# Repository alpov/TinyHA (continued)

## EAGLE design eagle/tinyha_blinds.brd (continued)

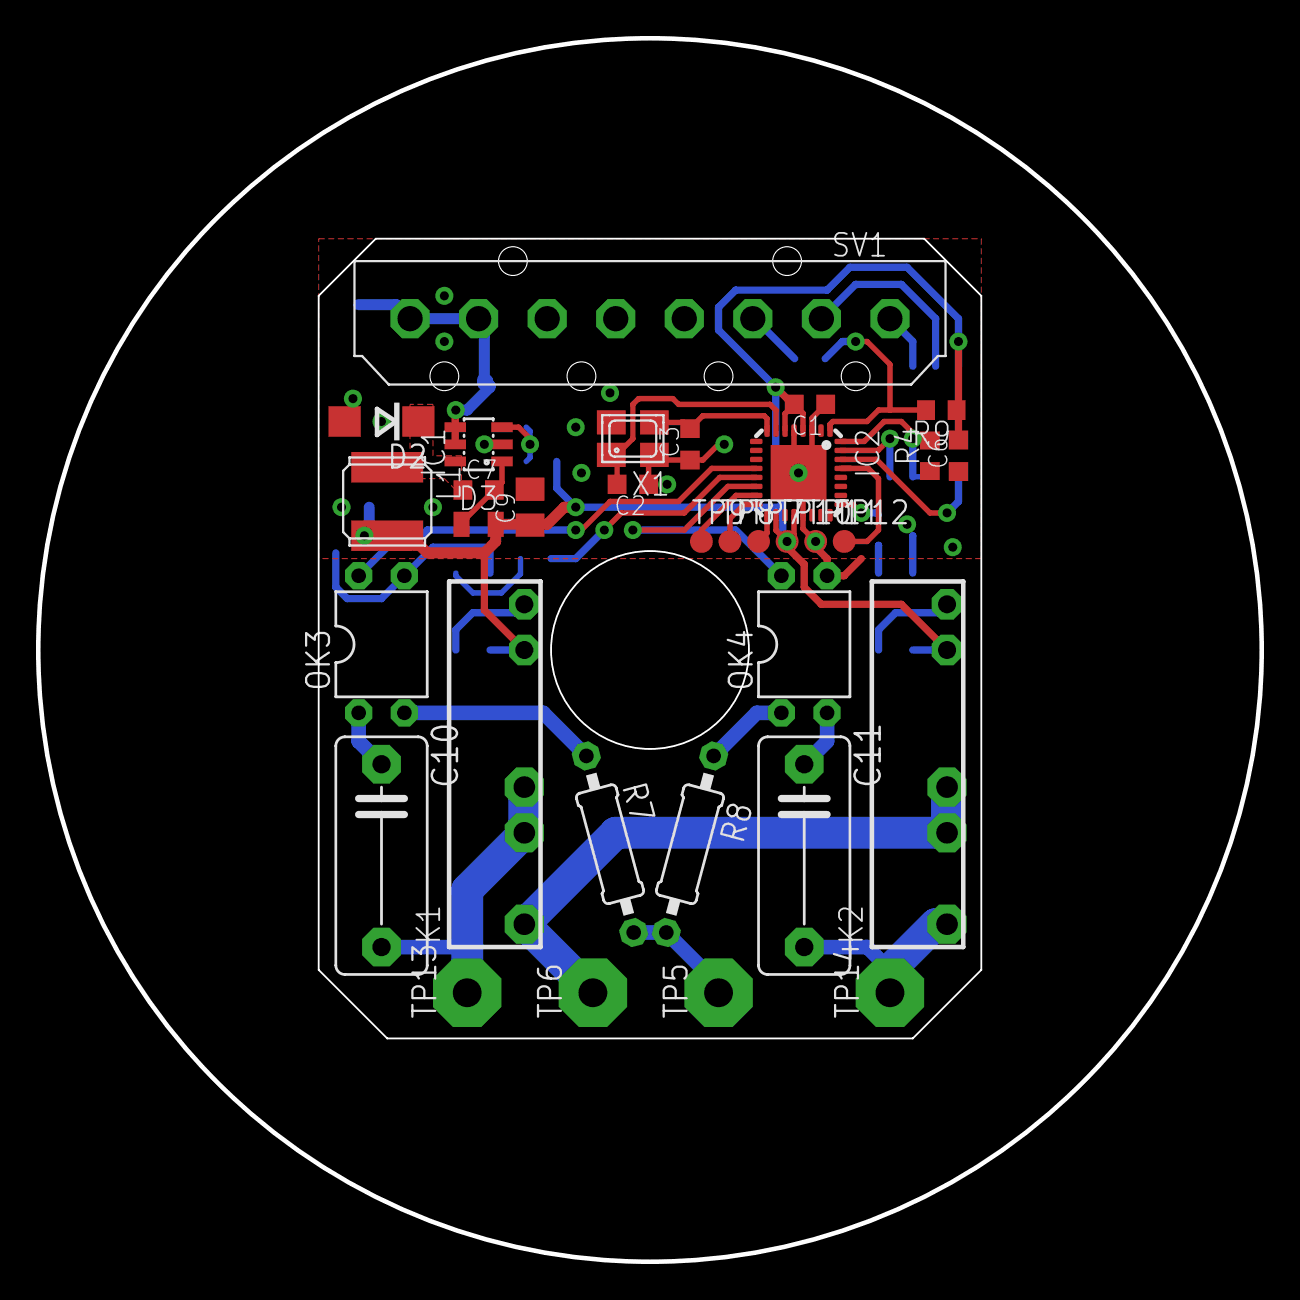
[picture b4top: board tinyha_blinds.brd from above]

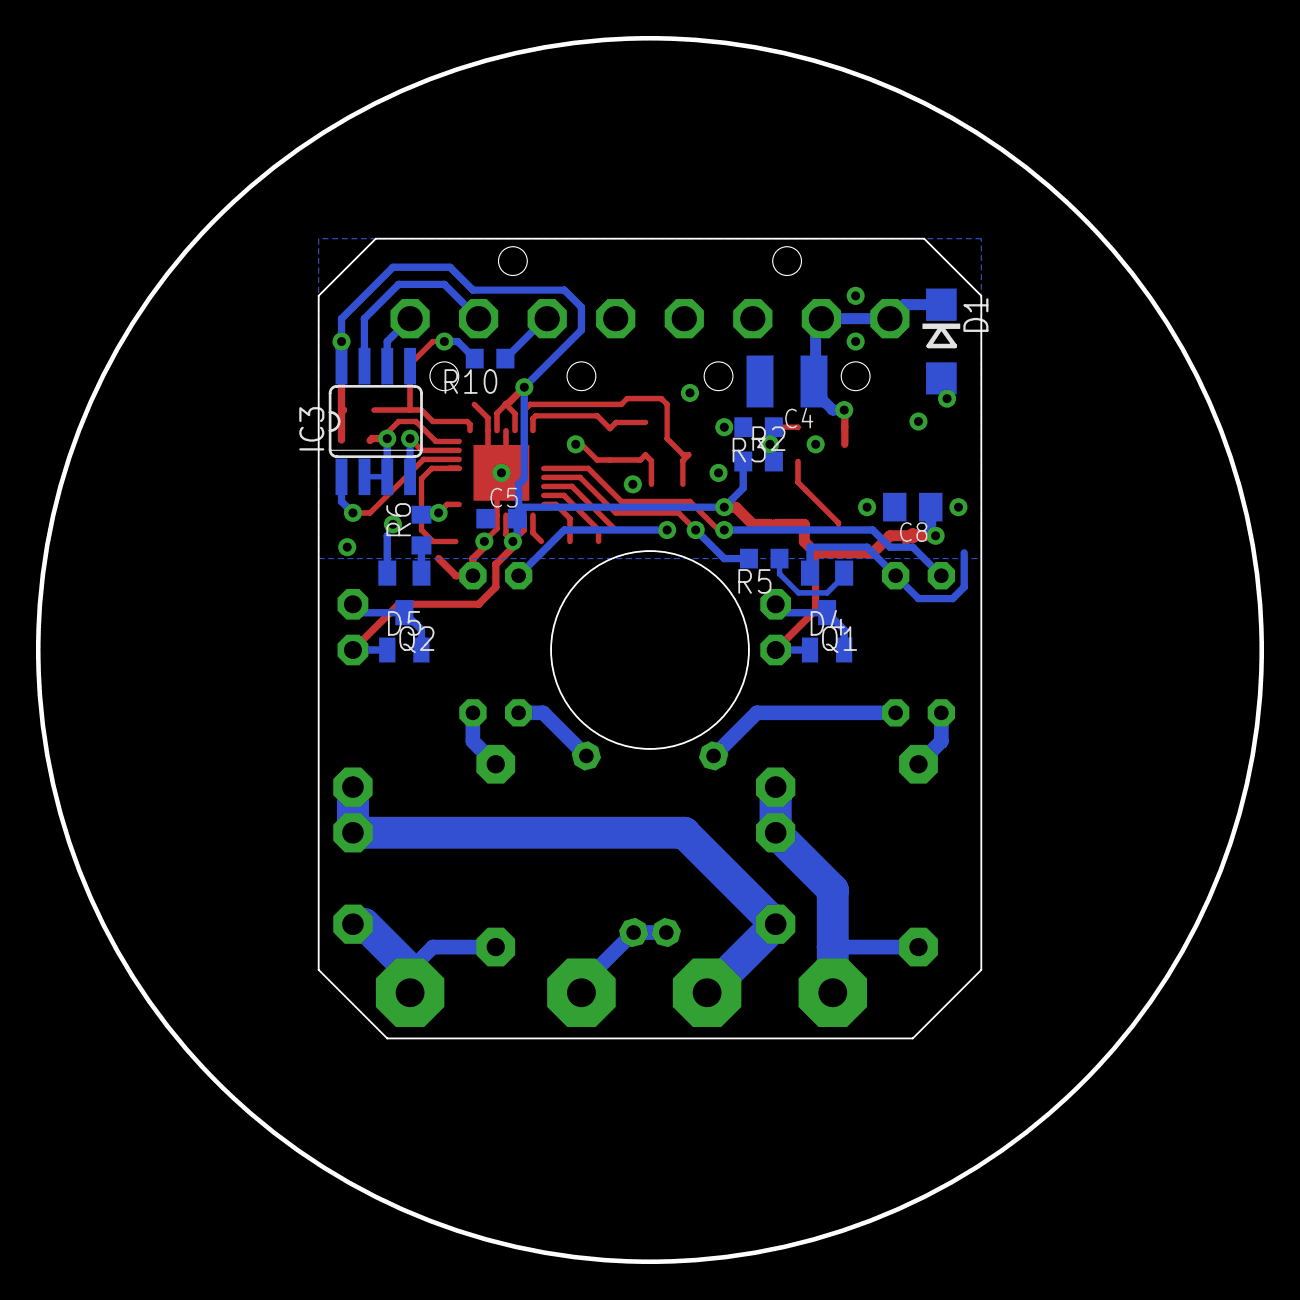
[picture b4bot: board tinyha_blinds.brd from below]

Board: 2 copper layers, 68.0 x 68.0 mm, 47 parts (14 on the bottom side), 35 nets.

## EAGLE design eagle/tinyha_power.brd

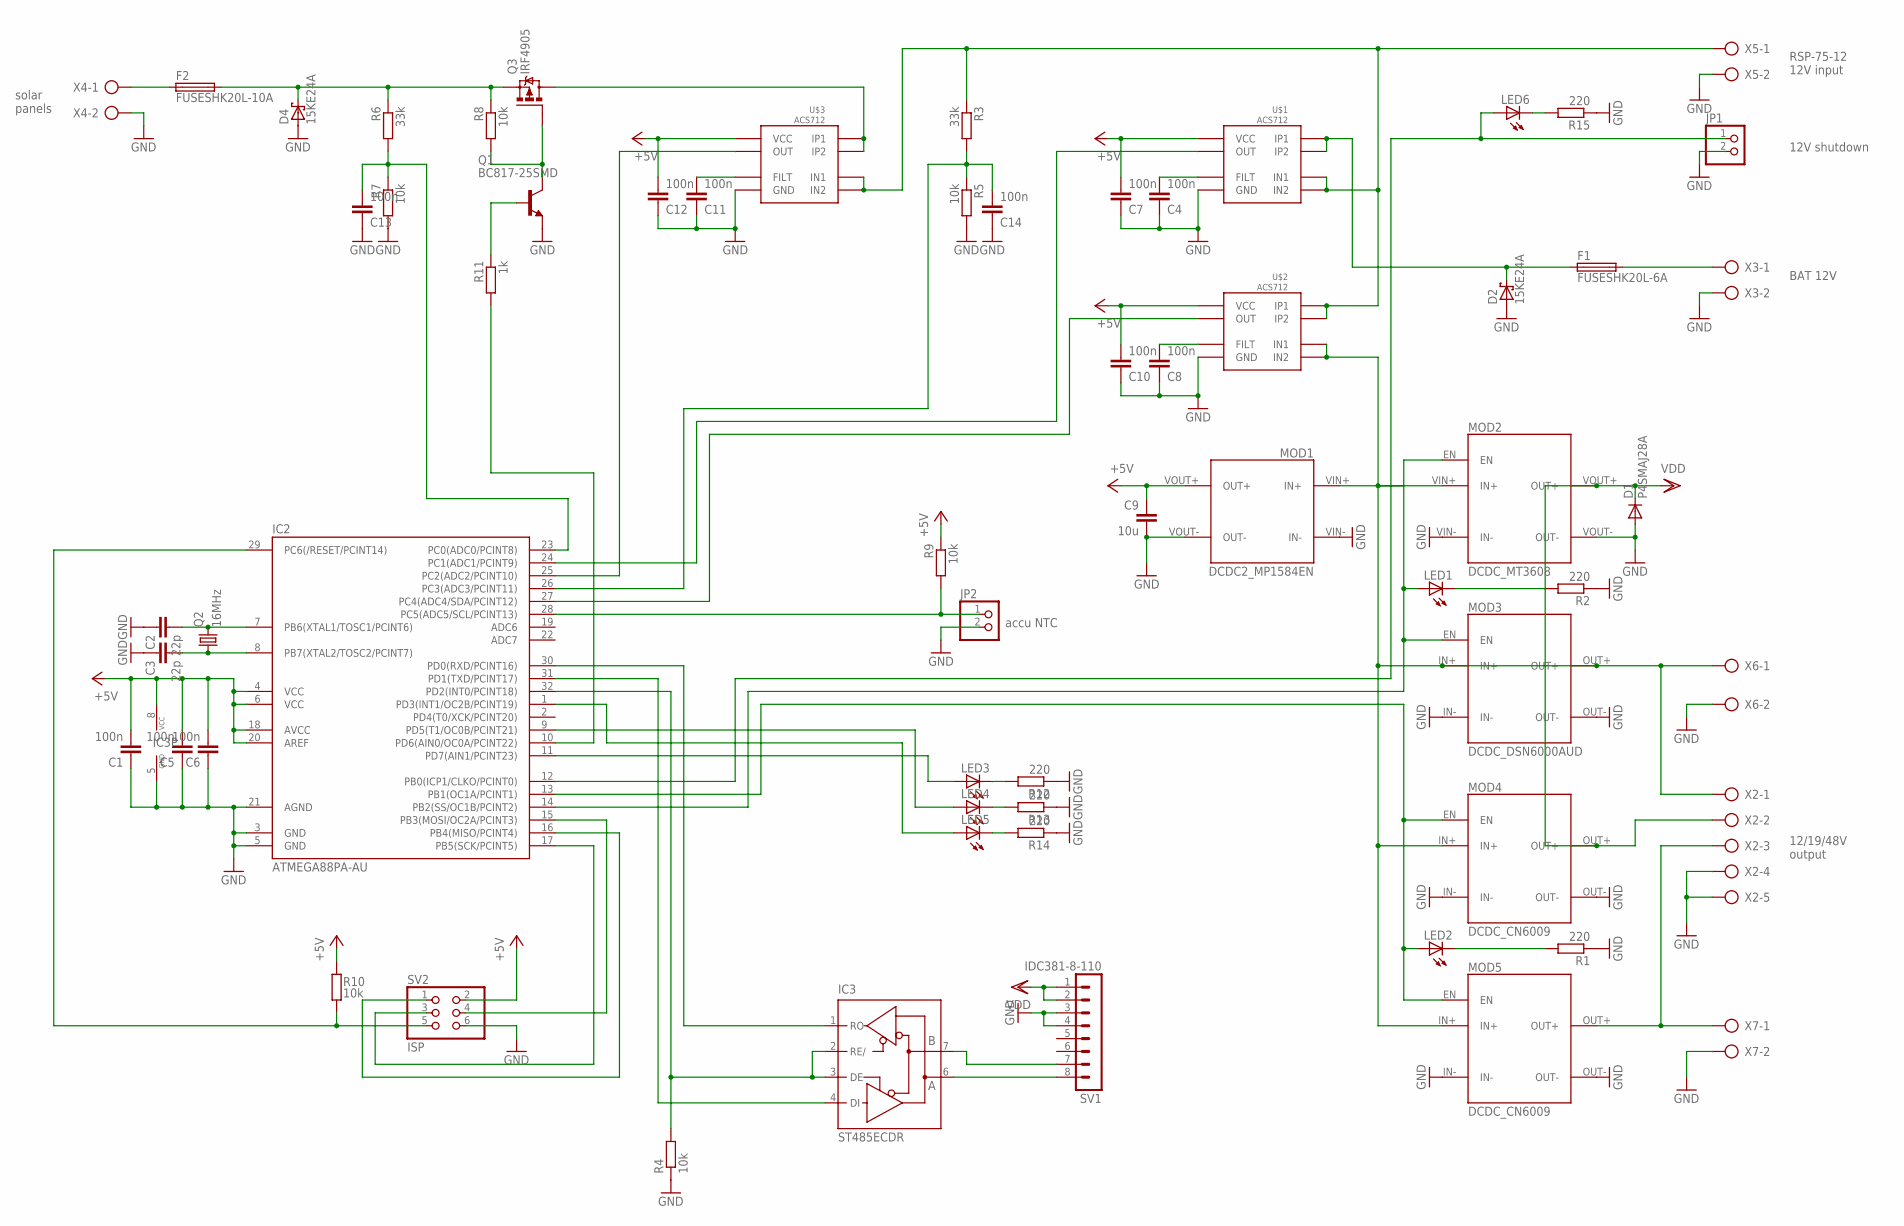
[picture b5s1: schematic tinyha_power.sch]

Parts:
C1, C5, C6: 100n; C0805K
C2, C3: 22p; C0805K
C4, C7, C8, C10, C11, C12, C13, C14: 100n; C0805
C9: 10u; C0805K
D1: P4SMAJ28A; DO214AC
D2, D4: 15KE24A; CB429-17
F1: FUSESHK20L-6A; SHK20L
F2: FUSESHK20L-10A; SHK20L
IC2: ATMEGA88PA-AU; TQFP32-08
IC3: ST485ECDR; SO08
JP1, JP2: PINHD-1X2; 1X02
LED1, LED2, LED3, LED4, LED5, LED6: LED3MM
MOD1: DCDC2_MP1584EN; DCDC_MP1584EN
MOD2: DCDC_MT3608
MOD3: DCDC_DSN6000AUD
MOD4, MOD5: DCDC_CN6009
Q1: BC817-25SMD; SOT23-BEC
Q2: 16MHz; HC49/S
Q3: IRF4905; TO220BH
R1, R2, R12, R13, R14, R15: 220; R0805
R3, R6: 33k; R0805
R4, R5, R7, R8, R9, R10: 10k; R0805
R11: 1k; R0805
SV1: IDC381-8-110; IDC381-8
SV2: ISP; 2X03/H
U$1, U$2, U$3: ACS712; SO8
X2: AK500/5
X3, X4, X5, X6, X7: AK500/2

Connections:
+5V: C1.2, C5.2, C6.2, C7.2, C9.1, C10.2, C12.2, IC2.4 (VCC), IC2.6 (VCC), IC2.18 (AVCC), IC2.20 (AREF), IC3.8 (VCC), MOD1.VOUT+ (OUT+), R9.1, R10.1, SV2.2, U$1.8 (VCC), U$2.8 (VCC), U$3.8 (VCC)
DIR: IC2.32 (PD2(INT0/PCINT18)), IC3.2 (RE/), IC3.3 (DE), R4.2
GND: C1.1, C2.1, C3.1, C4.1, C5.1, C6.1, C7.1, C8.1, C9.2, C10.1, C11.1, C12.1, C13.1, C14.1, D1.A, D2.A, D4.A, IC2.3 (GND), IC2.5 (GND), IC2.21 (AGND), IC3.5 (GND), JP1.2, JP2.2, MOD1.VIN- (IN-), MOD1.VOUT- (OUT-), MOD2.VIN- (IN-), MOD2.VOUT- (OUT-), MOD3.IN-, MOD3.OUT-, MOD4.IN-, MOD4.OUT-, MOD5.IN-, MOD5.OUT-, Q1.E, R1.1, R2.1, R4.1, R5.2, R7.2, R12.1, R13.1, R14.1, R15.1, SV1.3, SV1.4, SV2.6, U$1.5 (GND), U$2.5 (GND), U$3.5 (GND), X2.4, X2.5, X3.2, X4.2, X5.2, X6.2, X7.2
MOSI: IC2.15 (PB3(MOSI/OC2A/PCINT3)), SV2.4
unnamed: D4.C, F2.2A (2), Q3.S, R6.1, R8.1
unnamed: IC2.13 (PB1(OC1A/PCINT1)), LED2.A, MOD4.EN, MOD5.EN
unnamed: IC2.14 (PB2(SS/OC1B/PCINT2)), LED1.A, MOD2.EN, MOD3.EN
unnamed: LED2.K (C), R1.2
unnamed: LED1.K (C), R2.2
unnamed: IC2.11 (PD7(AIN1/PCINT23)), LED3.A
unnamed: C4.2, U$1.6 (FILT)
unnamed: D2.C, F1.1A (1), U$1.1 (IP1), U$1.2 (IP2)
unnamed: IC2.9 (PD5(T1/OC0B/PCINT21)), LED4.A
unnamed: IC3.7 (B), SV1.7
unnamed: LED6.K (C), R15.2
unnamed: C8.2, U$2.6 (FILT)
unnamed: IC3.6 (A), SV1.8
unnamed: MOD5.OUT+, X2.3, X7.1
unnamed: F1.2A (2), X3.1
unnamed: IC2.1 (PD3(INT1/OC2B/PCINT19)), LED5.A
unnamed: IC2.28 (PC5(ADC5/SCL/PCINT13)), JP2.1, R9.2
unnamed: MOD1.VIN+ (IN+), MOD2.VIN+ (IN+), MOD3.IN+, MOD3.OUT+, MOD4.IN+, MOD5.IN+, U$2.3 (IN1), U$2.4 (IN2), X2.1, X6.1
unnamed: C11.2, U$3.6 (FILT)
unnamed: C3.2, IC2.8 (PB7(XTAL2/TOSC2/PCINT7)), Q2.1
unnamed: Q1.C, Q3.G, R8.2
unnamed: C14.2, IC2.26 (PC3(ADC3/PCINT11)), R3.2, R5.1
unnamed: IC2.24 (PC1(ADC1/PCINT9)), U$1.7 (OUT)
unnamed: IC2.27 (PC4(ADC4/SDA/PCINT12)), U$2.7 (OUT)
unnamed: F2.1A (1), X4.1
unnamed: R3.1, U$1.3 (IN1), U$1.4 (IN2), U$2.1 (IP1), U$2.2 (IP2), U$3.3 (IN1), U$3.4 (IN2), X5.1
unnamed: C2.2, IC2.7 (PB6(XTAL1/TOSC1/PCINT6)), Q2.2
unnamed: Q3.D, U$3.1 (IP1), U$3.2 (IP2)
unnamed: IC2.25 (PC2(ADC2/PCINT10)), U$3.7 (OUT)
unnamed: C13.2, IC2.23 (PC0(ADC0/PCINT8)), R6.2, R7.1
unnamed: Q1.B, R11.1
unnamed: IC2.10 (PD6(AIN0/OC0A/PCINT22)), R11.2
unnamed: LED3.K (C), R12.2
unnamed: LED4.K (C), R13.2
unnamed: LED5.K (C), R14.2
unnamed: IC2.12 (PB0(ICP1/CLKO/PCINT0)), JP1.1, LED6.A
RESET: IC2.29 (PC6(/RESET/PCINT14)), R10.2, SV2.5
RXD: IC2.30 (PD0(RXD/PCINT16)), IC3.1 (RO)
SCK: IC2.17 (PB5(SCK/PCINT5)), SV2.3
TXD: IC2.31 (PD1(TXD/PCINT17)), IC3.4 (DI)
UH: IC2.16 (PB4(MISO/PCINT4)), SV2.1
VDD: D1.C, MOD2.VOUT+ (OUT+), MOD4.OUT+, SV1.1, SV1.2, X2.2

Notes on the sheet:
RSP-75-12 12V input
12/19/48V output
BAT 12V
solar panels
12V shutdown
accu NTC

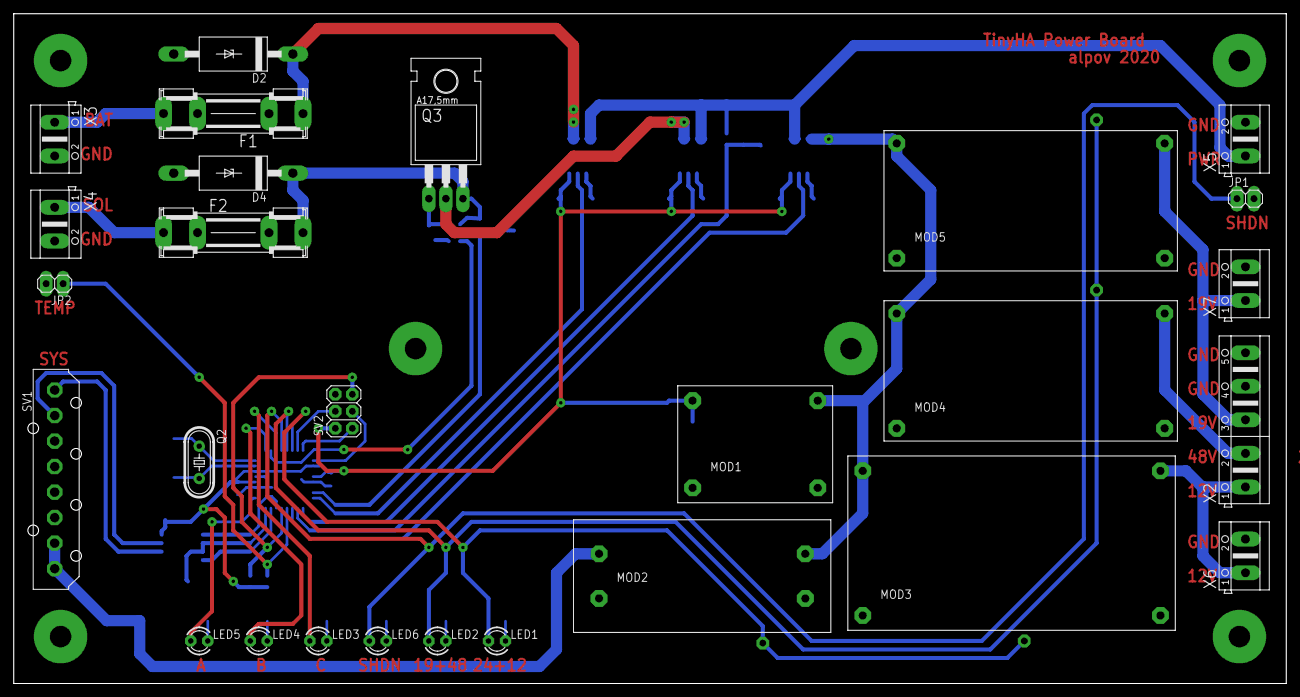
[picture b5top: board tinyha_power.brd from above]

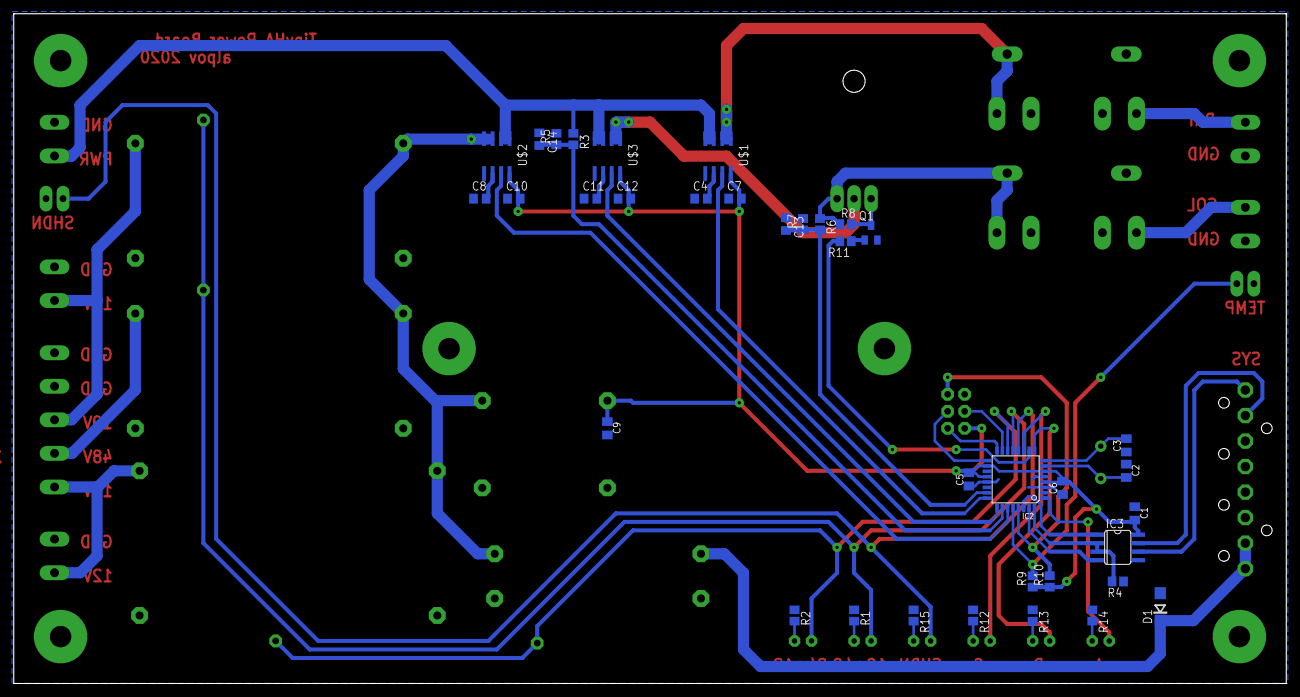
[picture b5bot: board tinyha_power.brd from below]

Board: 3 copper layers, 190.0 x 100.0 mm, 63 parts (36 on the bottom side), 46 nets.

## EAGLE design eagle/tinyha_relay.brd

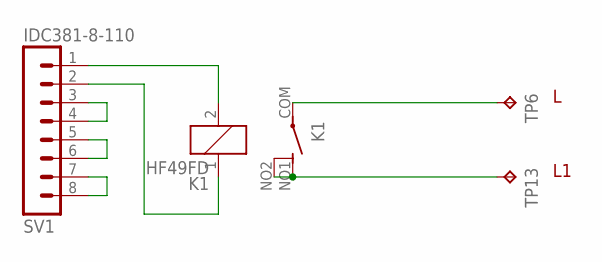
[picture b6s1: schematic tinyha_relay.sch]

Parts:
K1: HF49FD; HF49D
SV1: IDC381-8-110; IDC381-8
TP6, TP13: TP230; P1-20

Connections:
unnamed: SV1.5, SV1.6
unnamed: K1.NO1 (S1), K1.NO2 (S2), TP13.TP
unnamed: SV1.3, SV1.4
unnamed: K1.2, SV1.1
unnamed: K1.1, SV1.2
unnamed: SV1.7, SV1.8
unnamed: K1.COM, TP6.TP

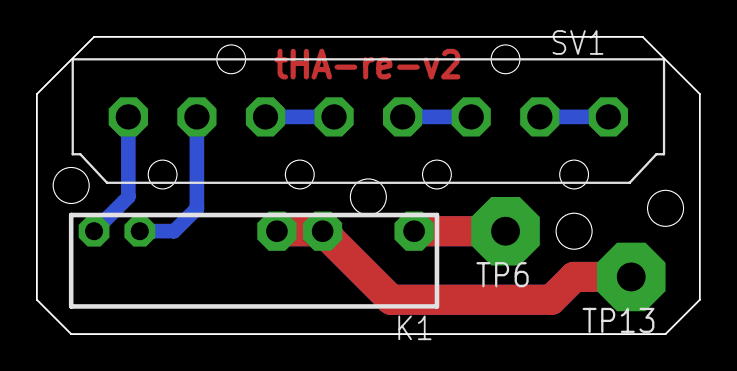
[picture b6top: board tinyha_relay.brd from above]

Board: 2 copper layers, 36.8 x 16.5 mm, 4 parts (0 on the bottom side), 7 nets.

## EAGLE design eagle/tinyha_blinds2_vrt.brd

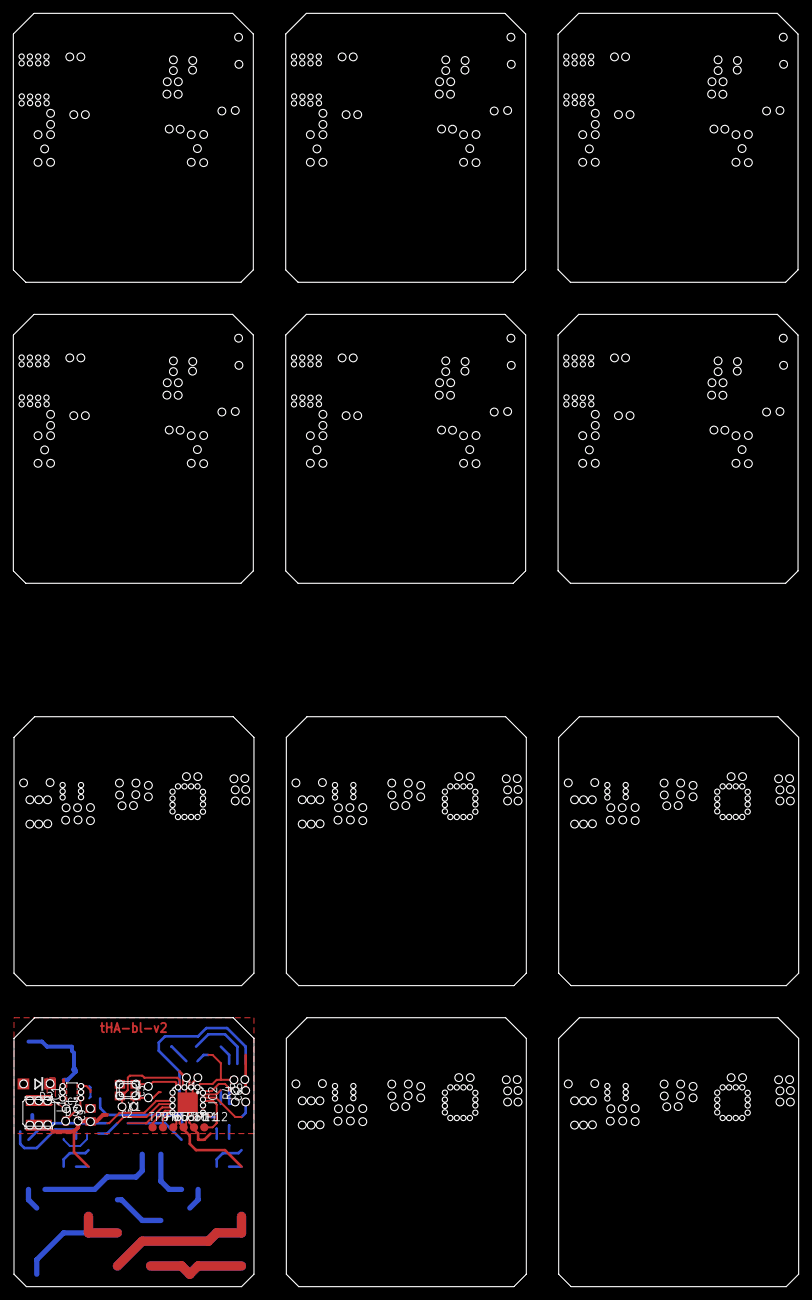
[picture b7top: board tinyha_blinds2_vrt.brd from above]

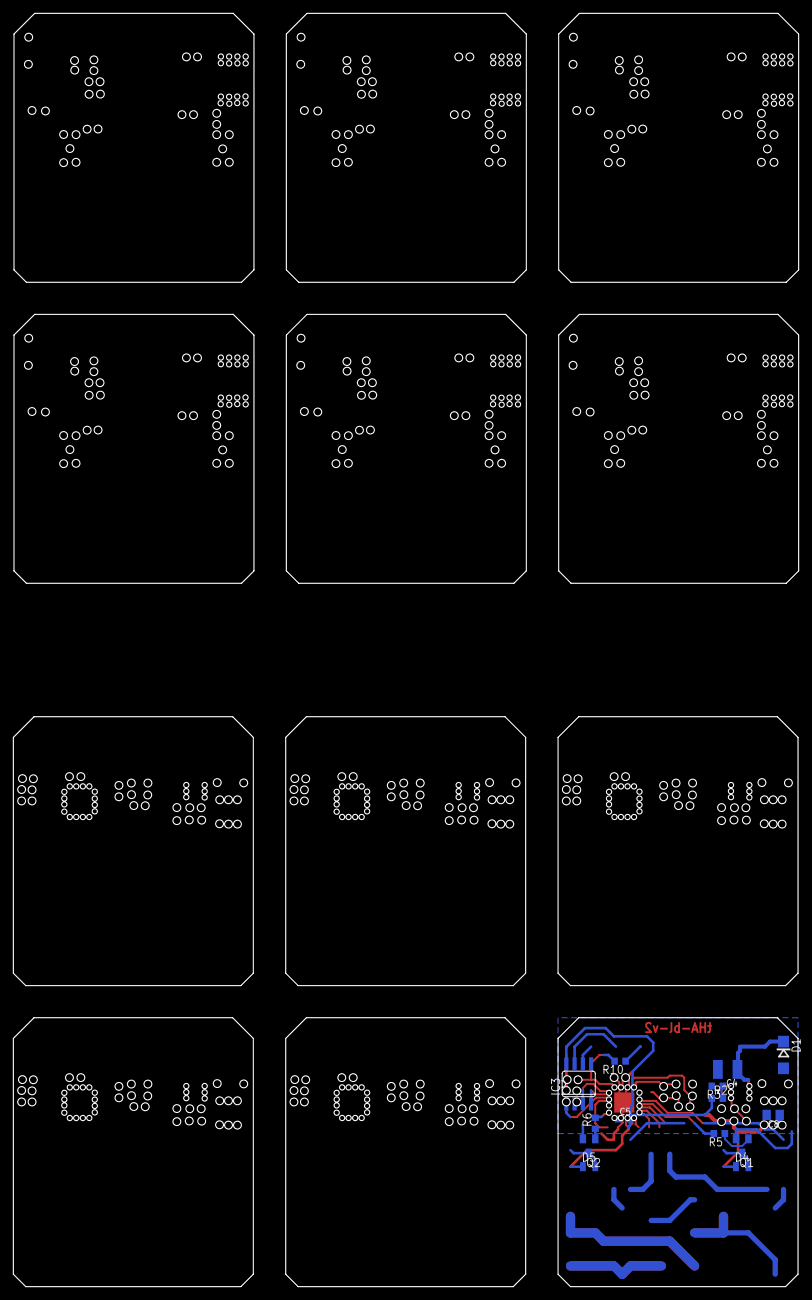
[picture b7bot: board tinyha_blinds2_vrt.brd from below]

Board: 2 copper layers, 120.5 x 195.4 mm, 34 parts (14 on the bottom side), 25 nets.

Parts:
C1, C5, C6, C7: 100n; C0603K
C2, C3: 22p; C0603K
C4: 10u/50V; C1210K
C8, C9: 10u; C0805K
D1: P4SMAJ28A; DO214AC
D2: SS14; DO214AC
D3, D4, D5: 1N4148; MICROMELF-W
IC1: MCP16301; SOT23-6L
IC2: ATMEGA88PA-AU; MLF32
IC3: ST485ECDR; SO08
L1: DJNR5040-150-S; DJNR5040
Q1, Q2: BC817-40SMD; SOT23-BEC
R2: 27k; R0603
R3: 5k1; R0603
R4: 10k; R0603
R5, R6: 1k; R0603
R9: 4k7; R0603
R10: 220; R0603
TP7, TP8, TP9, TP10, TP11, TP12: TPB1,27; B1,27
X1: ILCX13-FF5F18-16.0000; SMD3225

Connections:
+5V: C5.2, IC3.8, R2.1
DIR: IC3.2, IC3.3
GND: C1.1, C6.1, C8.2, C9.2, D1.A, D2.A, IC1.2, IC2.3, IC2.5, IC2.21, Q1.E, R4.1, TP11.TP, X1.4
unnamed: Q2.B, R6.1
unnamed: Q1.B, R5.1
unnamed: IC2.29, TP12.TP
unnamed: D5.A, Q2.C
unnamed: R2.2, R3.1
unnamed: IC2.15, TP9.TP
unnamed: IC2.1, R9.2
unnamed: C7.1, D2.C, IC1.6, L1.1
unnamed: D4.A, Q1.C
unnamed: C7.2, D3.C, IC1.1
unnamed: C3.2, IC2.8, X1.3
unnamed: C2.2, IC2.7, X1.1
S$3: C2.1, C3.1, X1.2
S$7: D5.C, IC2.18, IC2.20, TP10.TP
S$8: C1.2, IC2.4, IC2.6
S$10: C9.1, D3.A, D4.C, L1.2
S$11: C6.2, R9.1
S$13: IC2.32, R4.2
S$20: IC1.4, IC1.5
UH: IC2.16, TP8.TP
VDD: C4.1, D1.C
WH: IC2.17, TP7.TP

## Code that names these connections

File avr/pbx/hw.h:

#ifndef _HW_H
#define _HW_H

#define rs485_init()    DDRD |= _BV(PD2)
#define rs485_rx()      do { UCSR0B &= ~_BV(TXEN0); UCSR0B |= _BV(RXEN0); PORTD &= ~_BV(PD2); } while (0)
#define rs485_tx()      do { UCSR0B &= ~_BV(RXEN0); UCSR0B |= _BV(TXEN0); PORTD |=  _BV(PD2); } while (0)

#define led_comm(x)     /* not implemented */

#define aux_out(x)      do { if (x) PORTD |= _BV(PD5); else PORTD &= ~_BV(PD5); } while (0)

#define ring1(x)        do { if (x) PORTD |= _BV(PD3); else PORTD &= ~_BV(PD3); } while (0)
#define ring2(x)        do { if (x) PORTD |= _BV(PD4); else PORTD &= ~_BV(PD4); } while (0)
#define ring3(x)        do { if (x) PORTC |= _BV(PC0); else PORTC &= ~_BV(PC0); } while (0)
#define ring4(x)        do { if (x) PORTC |= _BV(PC2); else PORTC &= ~_BV(PC2); } while (0)
#define ring5(x)        do { if (x) PORTC |= _BV(PC4); else PORTC &= ~_BV(PC4); } while (0)

#define tone_out(x)     do { if (x) DDRB |= _BV(PB1); else DDRB &= ~_BV(PB1); } while (0)
#define tone_in(x)      (DDRB & _BV(PB1))

#define inverter1(x)    do { if (x) PORTD |= _BV(PD7); else PORTD &= ~_BV(PD7); } while (0)
#define inverter2(x)    do { if (x) PORTD |= _BV(PD6); else PORTD &= ~_BV(PD6); } while (0)

#define dtmf_stq()      (PINB & _BV(PB0))
#define dtmf_q()        ((PINB & (_BV(PB2) | _BV(PB3) | _BV(PB4) | _BV(PB5))) >> 2)

#define MUX_ONLY(x)     (x & 0x0f)
#define ADMUX_CLND1     (0x06)
#define ADMUX_CLND2     (0x07)
#define ADMUX_CLND3     (0x01)
#define ADMUX_CLND4     (0x03)
#define ADMUX_CLND5     (0x05)

#define ADDR_GROUP_ID   ADDR_UNIT_ID /* not used */
#define ADDR_UNIT_ID    (uint8_t*)E2END

#endif

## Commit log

2021-02-28 SVN revision 1300
2021-11-11 SVN revision 1367
